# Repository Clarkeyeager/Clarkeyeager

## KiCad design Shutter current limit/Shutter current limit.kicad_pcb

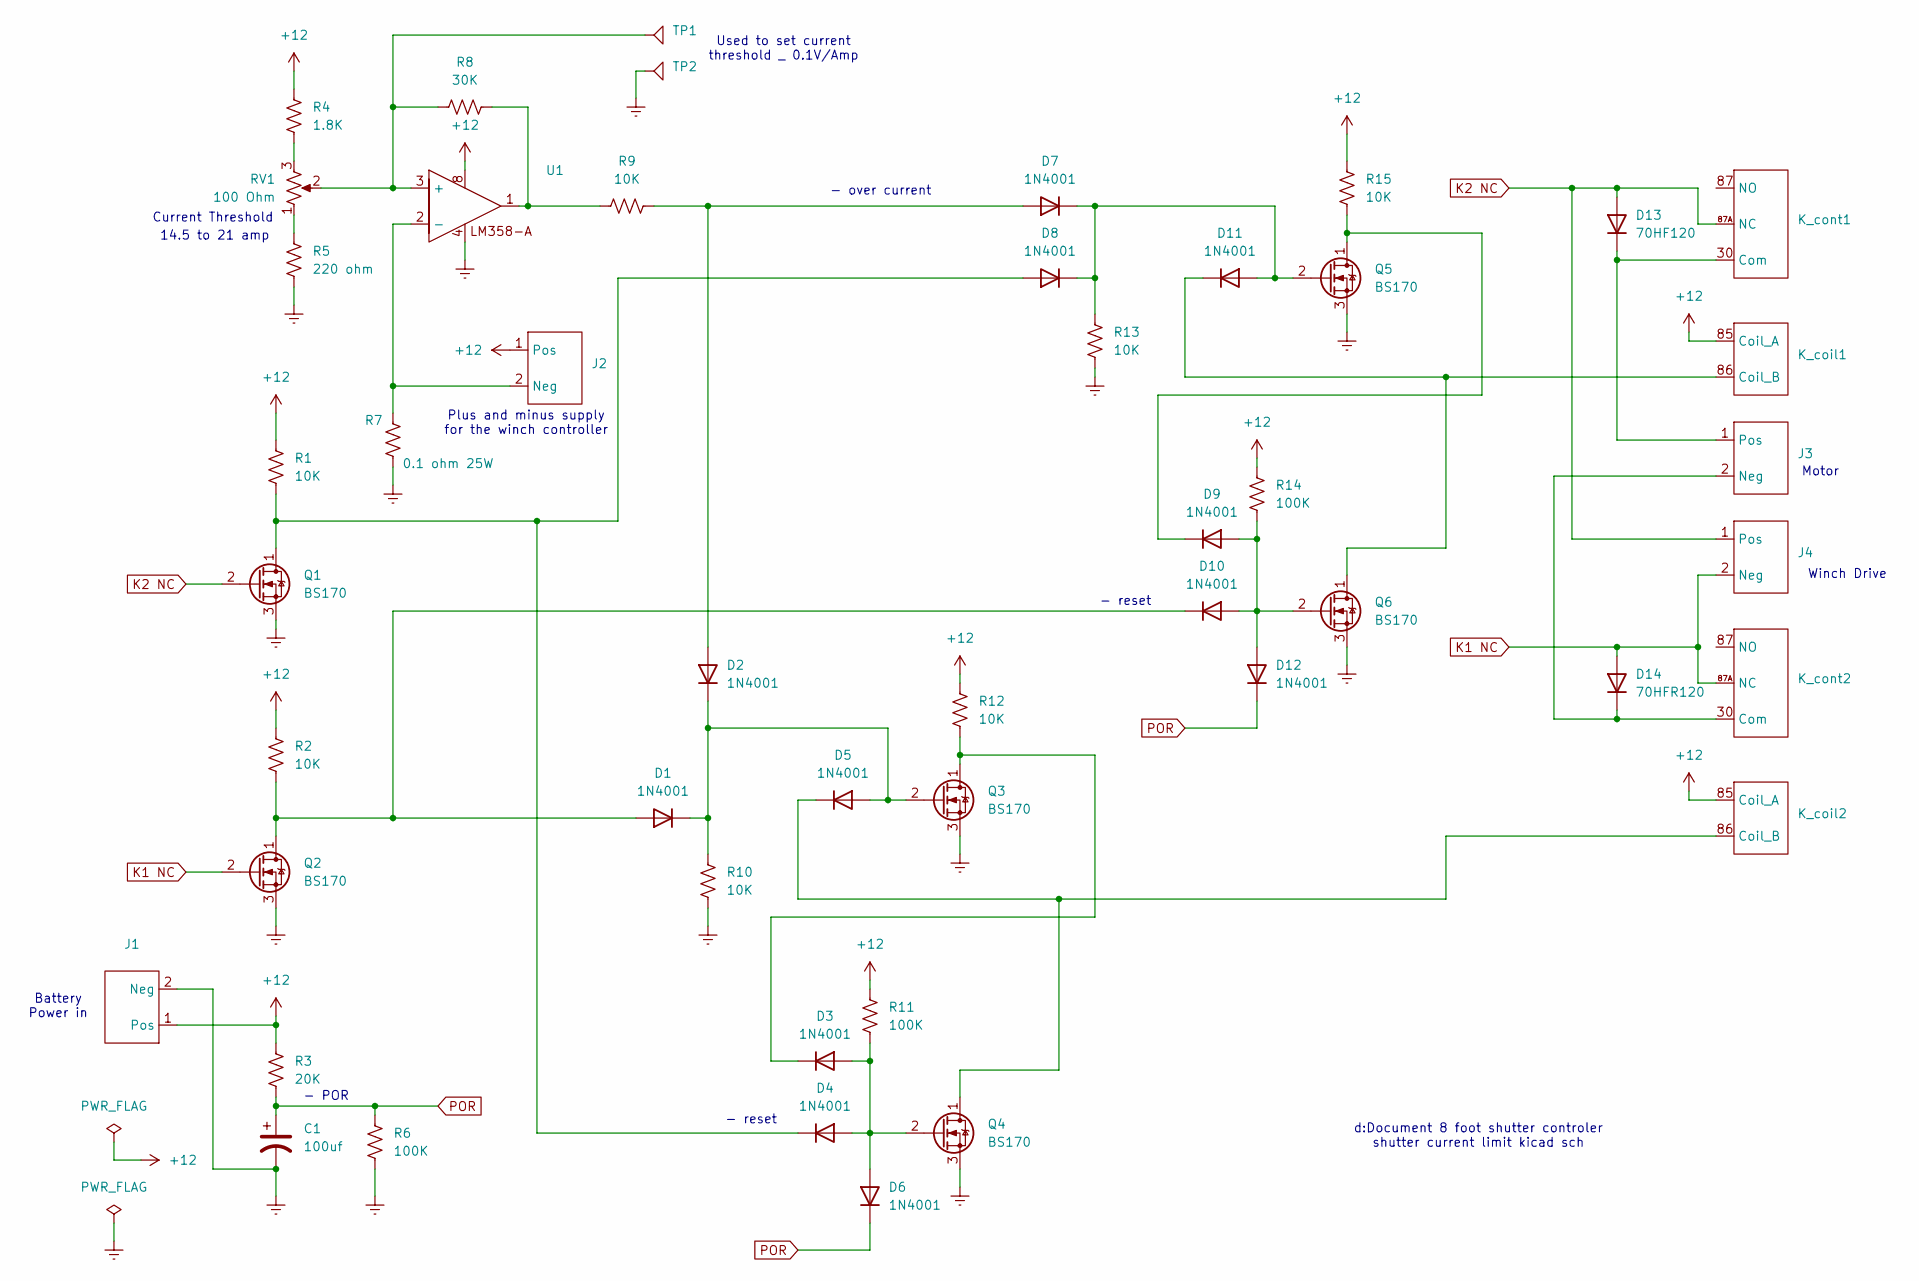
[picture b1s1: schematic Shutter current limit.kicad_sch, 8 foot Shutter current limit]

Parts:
C1: 100uf; 100Uf 35V
D1, D2, D3, D4, D5, D6, D7, D8, D9, D10, D11, D12: 1N4001
D13: 70HF120; diode_70HF120
D14: 70HFR120; diode_70HFR120
J1, J2, J3, J4: Conn_01x02_PWR
K_coil1, K_coil2: K_coil
K_cont1, K_cont2: RLY_Conn_01x03
Q1, Q2, Q3, Q4, Q5, Q6: BS170
R1, R2, R9, R10, R12, R13, R15: 10K; Resistor verticle
R3: 20K; Resistor verticle
R4: 1.8K; Resistor verticle
R5: 220 ohm; Resistor verticle
R6, R11, R14: 100K; Resistor verticle
R7: 0.1 ohm 25W; Resistor_0.10_ohm_25W
R8: 30K; Resistor verticle
RV1: 100 Ohm; POT
TP1, TP2: Test Point
U1: LM358

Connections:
+12: J1.1 (Pos), J2.1 (Pos), K_coil1.85 (Coil_A), K_coil2.85 (Coil_A), R1.1, R2.1, R3.1, R4.1, R11.1, R12.1, R14.1, R15.1, U1.8
Earth: C1.2, J1.2 (Neg), Q1.3 (S), Q2.3 (S), Q3.3 (S), Q4.3 (S), Q5.3 (S), Q6.3 (S), R5.2, R6.2, R7.2, R10.2, R13.2, TP2.1, U1.4
K1 NC: D14.1 (K), J4.2 (Neg), K_cont2.87A (NC), Q2.2 (G)
K2 NC: D13.2 (A), J4.1 (Pos), K_cont1.87A (NC), Q1.2 (G)
unnamed: D1.2 (A), D10.1 (K), Q2.1 (D), R2.2
unnamed: D1.1 (K), D2.1 (K), D5.2 (A), Q3.2 (G), R10.1
unnamed: D2.2 (A), D7.2 (A), R9.2
unnamed: D3.2 (A), D4.2 (A), D6.2 (A), Q4.2 (G), R11.2
unnamed: D3.1 (K), Q3.1 (D), R12.2
unnamed: D4.1 (K), D8.2 (A), Q1.1 (D), R1.2
unnamed: D5.1 (K), K_coil2.86 (Coil_B), Q4.1 (D)
unnamed: D9.1 (K), Q5.1 (D), R15.2
unnamed: D9.2 (A), D10.2 (A), D12.2 (A), Q6.2 (G), R14.2
unnamed: D7.1 (K), D8.1 (K), D11.2 (A), Q5.2 (G), R13.1
unnamed: D11.1 (K), K_coil1.86 (Coil_B), Q6.1 (D)
unnamed: D13.1 (K), J3.1 (Pos), K_cont1.30 (Com)
unnamed: D14.2 (A), J3.2 (Neg), K_cont2.30 (Com)
unnamed: J2.2 (Neg), R7.1, U1.2 (-)
unnamed: R4.2, RV1.3
unnamed: R5.1, RV1.1
unnamed: R8.2, R9.1, U1.1
unnamed: R8.1, RV1.2, TP1.1, U1.3 (+)
POR: C1.1, D6.1 (K), D12.1 (K), R3.2, R6.1

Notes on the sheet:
Used to set current threshold _ 0.1V/Amp
Winch Drive
- reset
Current Threshold
Plus and minus supply for the winch controller
- over current
d:Document 8 foot shutter controler shutter current limit kicad sch
- POR
Motor
Battery Power in
14.5 to 21 amp

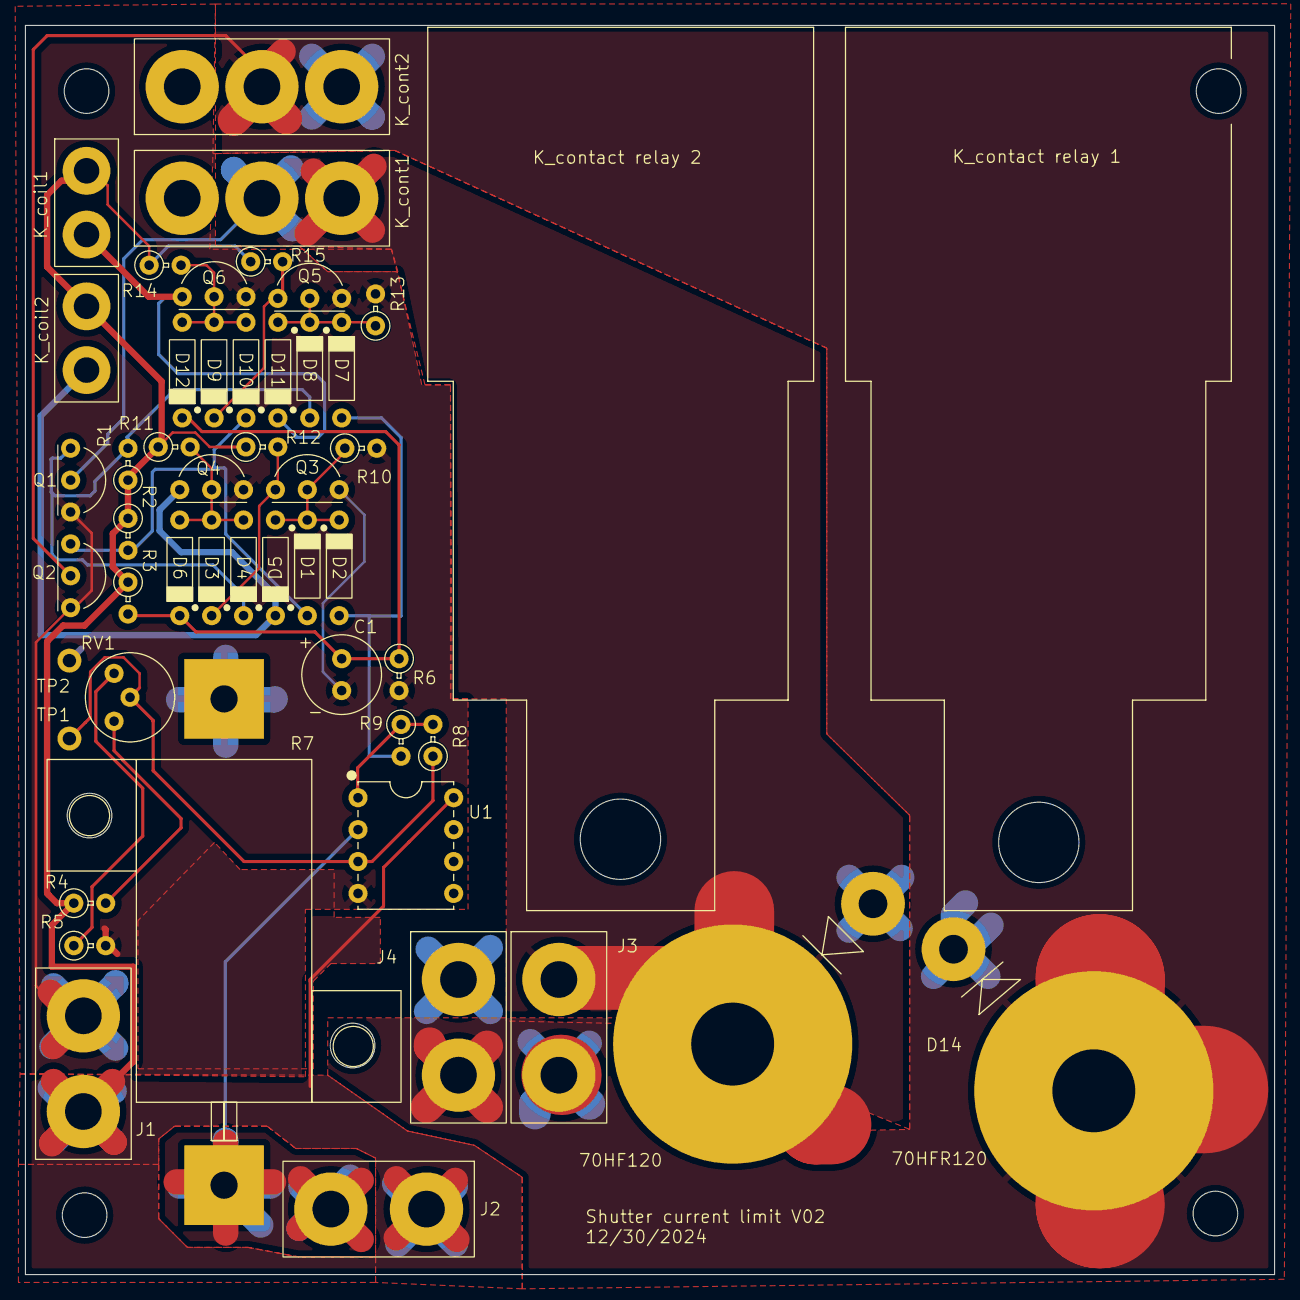
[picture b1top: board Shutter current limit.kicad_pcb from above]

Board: 2 copper layers, 99.5 x 99.5 mm, 48 parts (0 on the bottom side), 23 nets.
